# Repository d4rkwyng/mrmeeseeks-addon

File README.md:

# Mr MeeSeeks Shitty Addon

A #badgelife shitty addon PCB designed for DEF CON 26.

Created by @d4rkwyng and SparX. Thanks to [AND!XOR](https://www.andnxor.com/) for their instructional video on the schematics used in this project.

## Preview

| Front | Back |
|:-:|:-:|
|  |  |

## Bill of Materials

Rev E (see `mrmeeseeks_RevE_BOM.csv`). Rev A–D boards carry a ninth LED/resistor pair (D9/R9) and an 0402 C1.

| Ref | Component | Package | Qty |
|-----|-----------|---------|-----|
| U1 | MCP23017 | SOIC-28 (`mrmeeseeks_RevE`) or SSOP-28 (`mrmeeseeks_RevE_ESO`) | 1 |
| D1-D8 | LED | 1206 | 8 |
| R1-R8 | 220 ohm | 1206 | 8 |
| C1 | 0.1uF | 1206 | 1 |
| X1 | Shitty connector | 2x2 | 1 |

## Hardware Notes (Rev E)

- **I2C address `0x20`** — MCP23017 A0/A1/A2 are all tied to GND (`0100 A2 A1 A0`). Bus runs at the badge's 3.3 V.
- **LEDs on GPB0–GPB7** (D1–D8 via R1–R8 to GND), active high: set IODIRB = `0x00`, then write GPIOB/OLATB. Port A (GPA0–GPA7), INTA and INTB are unconnected; RESET is tied to 3.3 V.
- **Connector** follows the original 2x2 badgelife add-on layout (front view: VCC/SDA top row, GND/SCL bottom row). The footprint numbers its pads 1=VCC, 2=GND, 3=SCL, 4=SDA; only the physical positions matter for this 2x2 standard.
- `mrmeeseeks_RevE.net` is a stale 2018 netlist that still lists the Rev D D9/R9 pair — do not re-import it into the Rev E boards.
- On Rev A–D, D9/R9 is driven from GPA0 (pin 21). Both Rev E boards still carry that net name (`Net-(R9-Pad1)`) on U1 pin 21, but nothing else is on the net and it has no copper, so the pin is unconnected.
- `mrmeeseeks_RevE_BOM.csv` lists the SOIC board (`mrmeeseeks_RevE.kicad_pcb`). For the SSOP board, U1 is `MCP23017-ESS_NoSilk` instead; every other line is the same.

## Fabrication Outputs

All gerbers were plotted with KiCad 4.0.7 in 2018.

- `gerbers/mrmeeseeks_RevE-*` (SOIC board; `mrmeeseeks_RevE.zip` holds the same files) were plotted 2018-06-13, before commit `aacb9ba` (2018-06-18) moved U1's `MCP23017` value text from B.SilkS to B.Fab. The only difference from the current board is that text: it is still in `mrmeeseeks_RevE-B.SilkS.gbo`, drawn in 0.05 mm strokes inside U1's outline. Copper, mask, paste, edge cuts and drill match the current board.
- `gerbers/mrmeeseeks_RevE_ESO-*` (SSOP board) were plotted from the board as committed in `7509748`. There is no zip for this set.
- Both Rev E boards use a 0.2 mm pad-to-mask clearance. On the SSOP board this makes each U1 mask opening 0.83 mm wide at a 0.65 mm pin pitch, so there is no solder-mask web between U1 pins. On the SOIC board the web is about 0.11 mm.

## Revisions

- **Rev E** — Final revision, two board variants sharing `mrmeeseeks_RevE.sch`:
  - `mrmeeseeks_RevE.kicad_pcb` — MCP23017 in SOIC-28 (`MCP23017-ESO_NoSilk`, 1.27 mm pitch)
  - `mrmeeseeks_RevE_ESO.kicad_pcb` — MCP23017 in **SSOP-28** (`MCP23017-ESS_NoSilk`, 0.65 mm pitch), despite the "ESO" in the filename
- **Rev D** — PCB only (no schematic in repo); gerbers in `gerbers/mrmeeseeks_RevD.zip`
- **Rev B, Rev C** — PCB only
- **Rev A** — Initial prototype (schematic `mrmeeseeks_RevA.sch` + PCB)

## Project Structure

```
mrmeeseeks-addon/
├── design/          # Artwork, silkscreen, and soldermask KiCad footprints
├── gerbers/         # Manufacturing files (Rev D, Rev E, Rev E SSOP variant)
├── lib/             # KiCad component libraries
└── mrmeeseeks_*     # Schematic, PCB, and netlist files
```

## Tools

- [KiCad](https://www.kicad.org/) — Schematic and PCB design

## License

MIT License. See [LICENSE](LICENSE) file.

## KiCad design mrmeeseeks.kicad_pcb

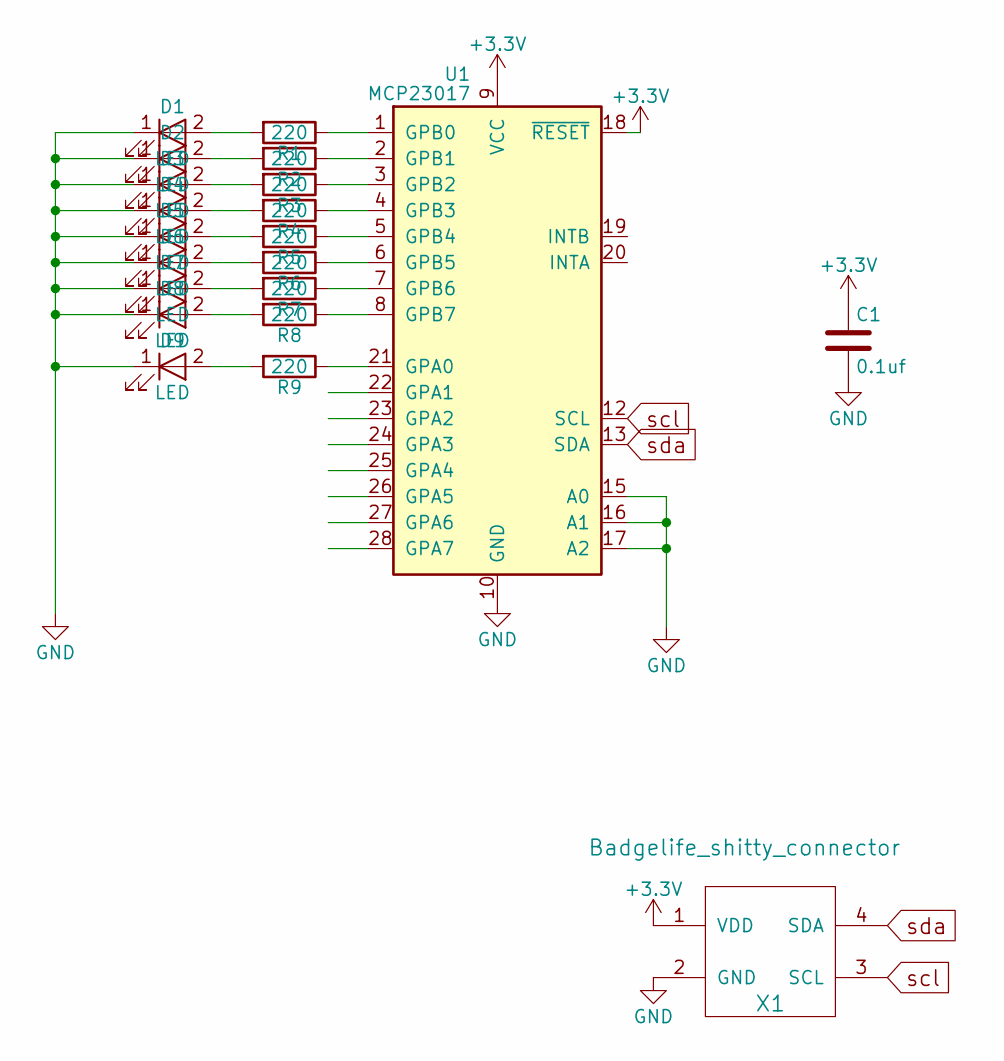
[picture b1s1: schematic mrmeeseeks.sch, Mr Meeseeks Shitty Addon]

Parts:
C1: 0.1uf; C_0402_NoSilk
D1, D2, D3, D4, D5, D6, D7, D8, D9: LED; LED_1206_HandSoldering
R1, R2, R3, R4, R5, R6, R7, R8, R9: 220; R_1206_HandSoldering
U1: MCP23017; SOIC-28
X1: Badgelife_shitty_connector; Badgelife-Shitty-2x2

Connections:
+3V3: C1.1, U1.9 (VCC), U1.18 (~RESET), X1.1 (VDD)
GND: C1.2, D1.1 (K), D2.1 (K), D3.1 (K), D4.1 (K), D5.1 (K), D6.1 (K), D7.1 (K), D8.1 (K), D9.1 (K), U1.10 (GND), U1.15 (A0), U1.16 (A1), U1.17 (A2), X1.2 (GND)
unnamed: D1.2 (A), R1.2
unnamed: D2.2 (A), R2.2
unnamed: D3.2 (A), R3.2
unnamed: D4.2 (A), R4.2
unnamed: D5.2 (A), R5.2
unnamed: D6.2 (A), R6.2
unnamed: D7.2 (A), R7.2
unnamed: D8.2 (A), R8.2
unnamed: D9.2 (A), R9.2
unnamed: R1.1, U1.1 (GPB0)
unnamed: R2.1, U1.2 (GPB1)
unnamed: R3.1, U1.3 (GPB2)
unnamed: R4.1, U1.4 (GPB3)
unnamed: R5.1, U1.5 (GPB4)
unnamed: R6.1, U1.6 (GPB5)
unnamed: R7.1, U1.7 (GPB6)
unnamed: R8.1, U1.8 (GPB7)
unnamed: R9.1, U1.21 (GPA0)
scl: U1.12 (SCL), X1.3 (SCL)
sda: U1.13 (SDA), X1.4 (SDA)

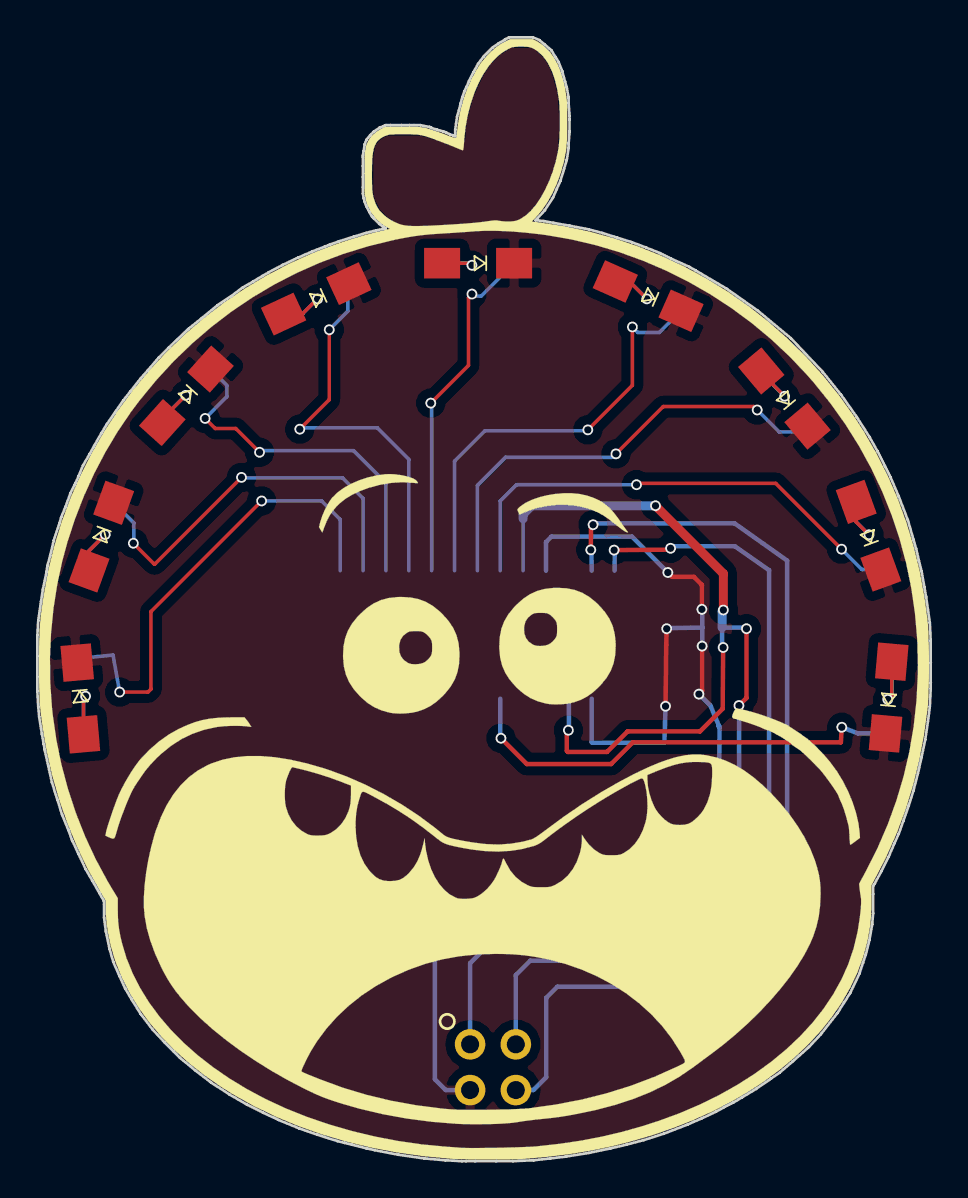
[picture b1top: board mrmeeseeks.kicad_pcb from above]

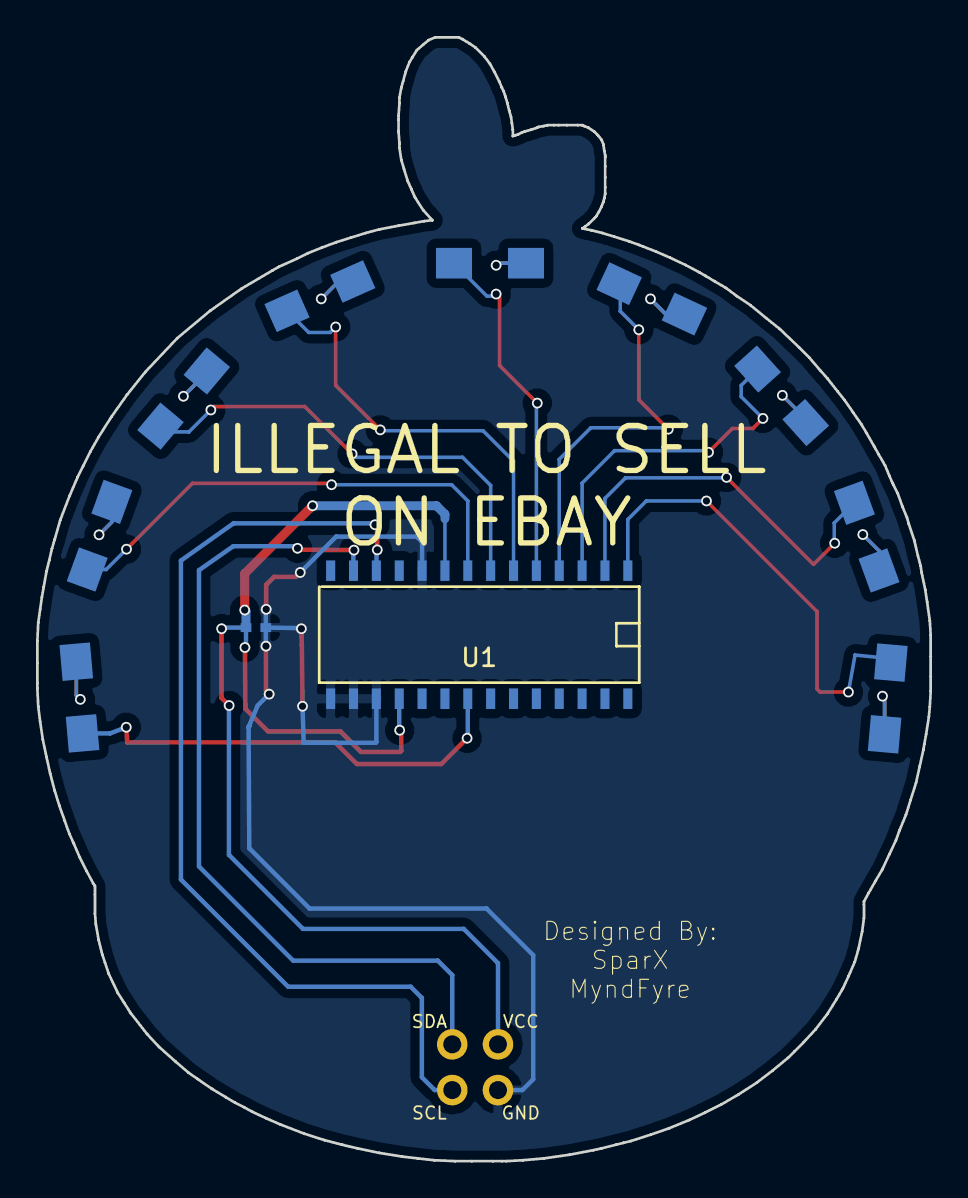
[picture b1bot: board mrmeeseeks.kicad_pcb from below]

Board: 2 copper layers, 49.6 x 62.4 mm, 21 parts (11 on the bottom side), 22 nets.

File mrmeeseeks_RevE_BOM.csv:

"Id";"Designator";"Package";"Quantity";"Designation";"Supplier and ref";
1;"G***";"soldermask";1;"LOGO";;;
2;"G***";"silkscreen";1;"LOGO";;;
3;"X1";"Badgelife-Shitty-2x2";1;"Badgelife_shitty_connector";;;
4;"R6,R1,R2,R3,R4,R5,R7,R8";"R_1206_HandSoldering_NoSilk";8;"220";;;
5;"D1,D2,D3,D4,D5,D6,D7,D8";"LED_1206_HandSoldering_MinSilk";8;"LED";;;
6;"U1";"MCP23017-ESO_NoSilk";1;"MCP23017";;;
7;"C1";"C_1206_HandSoldering";1;"0.1uf";;;
8;"G***";"smwyg";1;"LOGO";;;
9;"G***";"d4rkwyng";1;"LOGO";;;
10;"G***";"d4rkwyng_solder";1;"LOGO";;;

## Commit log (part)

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2018-05-19 MrMeesee Images
2018-05-20 Image Update
2018-05-29 Schematic Complete
2018-05-29 Edge Cuts to PCB
2018-05-30 Updated PCB Design
2018-05-31 Draft 1 of PCB Done
    All tracers added
2018-05-31 Gerbers Added
2018-05-31 Design By Updates
2018-05-31 Removed Totem
2018-05-31 CleanUp
2018-05-31 Updates to Soldermask Layer
2018-05-31 PSD Updates
2018-05-31 Readme Update
2018-05-31 Draft 2
    Redesigned tracers
2018-05-31 Updated Example Image
2018-05-31 Updated Traces
2018-05-31 Added traces to Front as Gerber2
    Backup is original PCB file.
2018-05-31 No Trace PCB
    Classified as Original
2018-06-01 Revision D
    No holes on front for traces
2018-06-02 Rev C committed
2018-06-02 Revision Tagging
2018-06-02 Clean Up
2018-06-02 Rev D Updates
2018-06-02 Readme updates
2018-06-06 Update to Naming Structure
2018-06-13 Revision E
2018-06-13 Project Updates
2018-06-13 Show Me What You've Got Update
2018-06-13 Gerbers
2018-06-13 The terror that flaps in the night!
2018-06-18 Minor Library Changes
2018-06-18 Rev E ESO Version
2018-06-18 ESO Gerber
2024-03-07 MrMeeseek Images
2024-03-07 Revert "ESO Gerber"
    This reverts commit d02b66e383884bd23c169393c7deaf4388623bbe.
